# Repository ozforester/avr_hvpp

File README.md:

# avr_hvpp

Simple hvpp programmer on atmega8 and 1602A lcd with twi extention<br>

Kicad schematics and pcb's are placed in hardware folder.
Sure you can even plug mega328 into master socket and<br>
write your code in arduino ide and modify pcb for another package.<br>
Kicad is the most useful tool to change things you like<br>

I'm thinking about coding main menu in C and others: <br>
lcd, twi, adc and hvpp libraries in assembly.<br>
Pure C version I coded was compiled to 8k (w/o a few bytes)<br>
Assembly version is changing now. If you need test one working<br>
You can find a hex file named chiphealer.hex on hardware folder.<br>
Some more errors has to be fixed and I may commit its gas version too<br>

All work except kicad were processed on orange pc.<br>
It's very hard to edit pcb and schematics on orange<br>
(opengl works and 3d model turns but don't do that,<br>
really, beleve me)

And more. I'm learning now. Doing a lot of compromised<br>
steps in programming. These are like a practical answers<br>
to some questions and thus not perfect<br>

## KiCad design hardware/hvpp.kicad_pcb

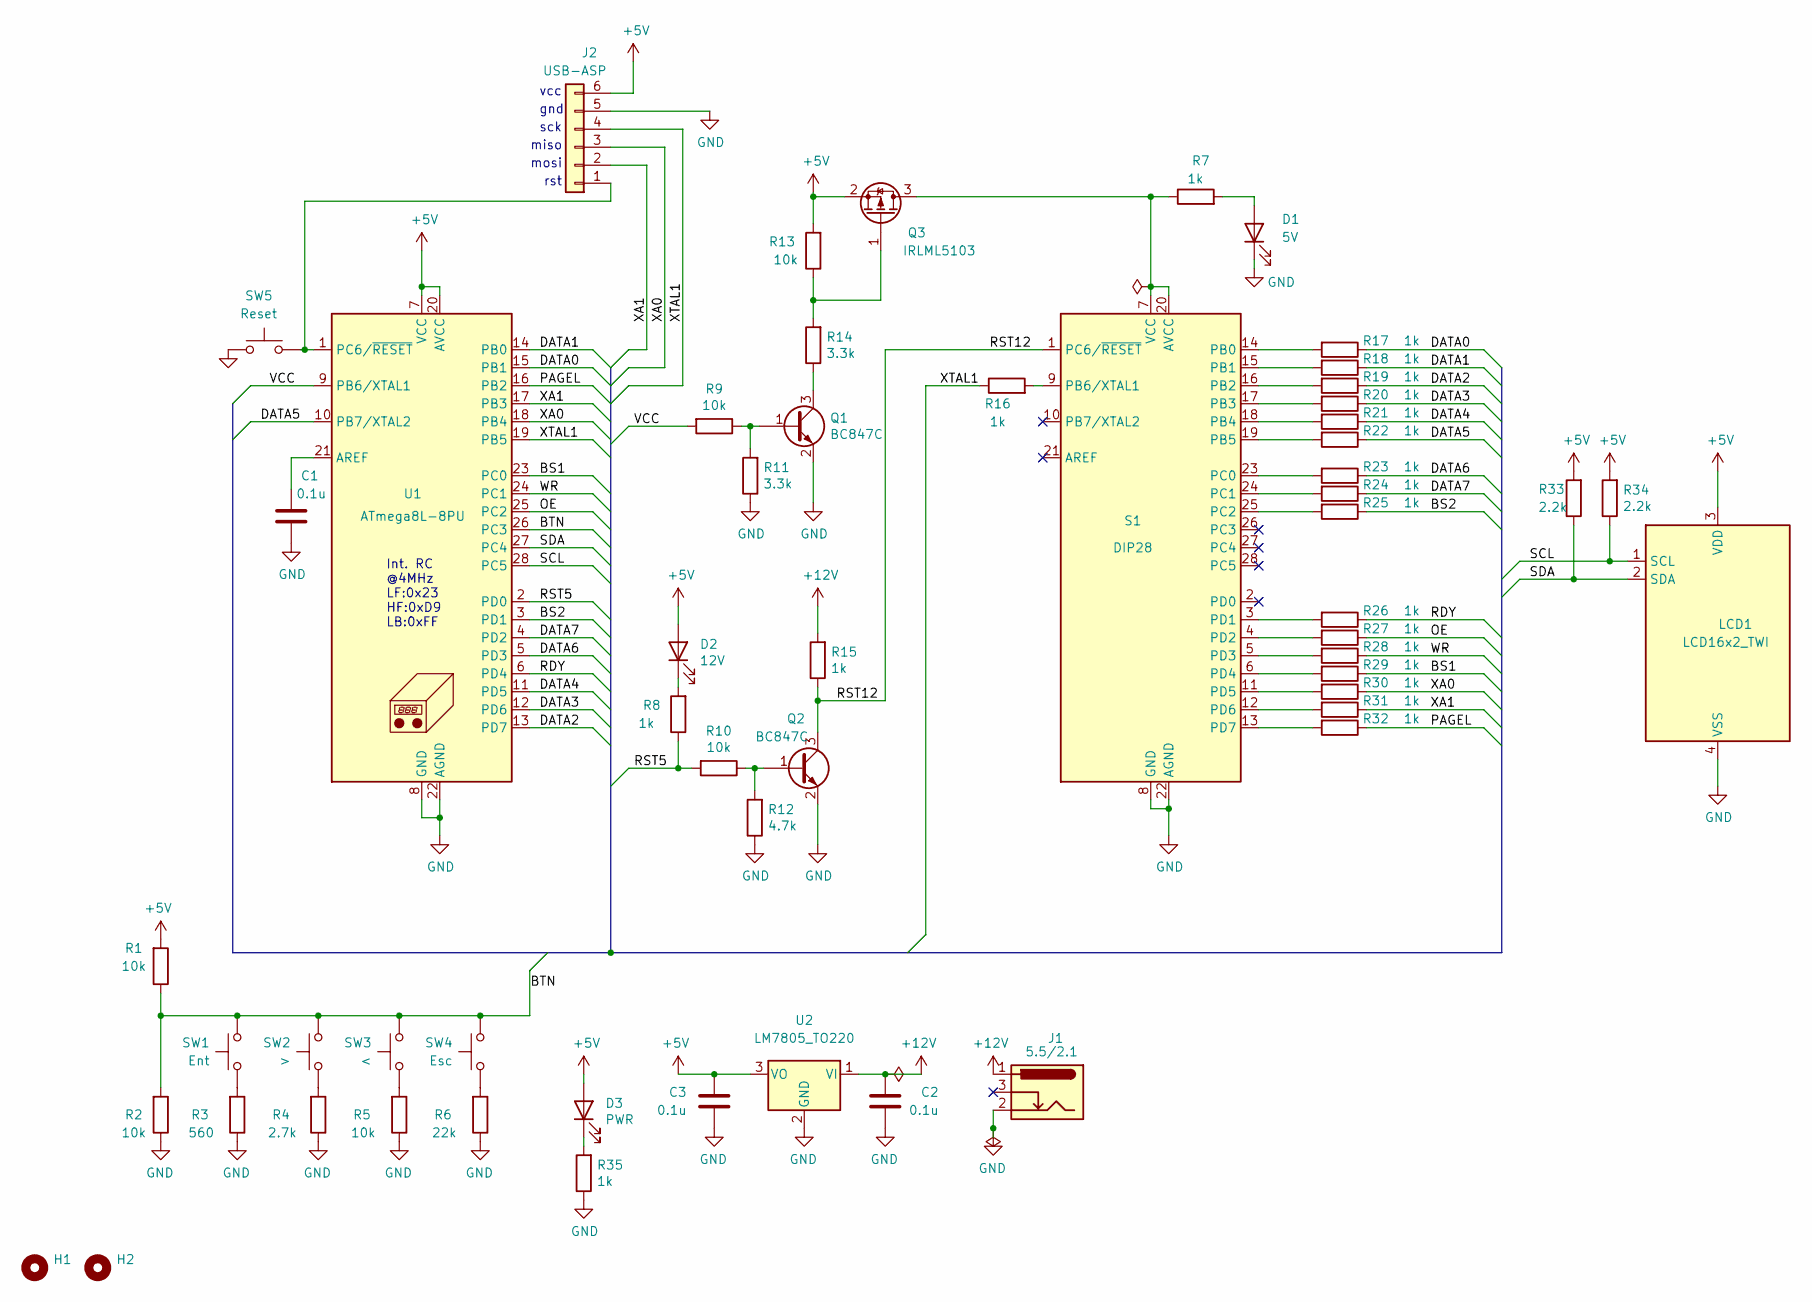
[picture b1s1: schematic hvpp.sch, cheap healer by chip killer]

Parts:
C1, C2, C3: 0.1u; C_0805_2012Metric_Pad1.15x1.40mm_HandSolder
D1: 5V; R_0805_2012Metric_Pad1.15x1.40mm_HandSolder
D2: 12V; R_0805_2012Metric_Pad1.15x1.40mm_HandSolder
D3: PWR; R_0805_2012Metric_Pad1.15x1.40mm_HandSolder
H1, H2: MountingHole; MountingHole_2.2mm_M2_DIN965_Pad
J1: 5.5/2.1; barreljack
J2: USB-ASP; PinHeader_1x06_P2.54mm_Vertical
LCD1: LCD16x2_TWI; 1602A
N1: Housing; DIP-28_W7.62mm
Q1, Q2: BC847C; SOT-23
Q3: IRLML5103; SOT-23
R1, R2, R5, R9, R10, R13: 10k; R_0805_2012Metric_Pad1.15x1.40mm_HandSolder
R3: 560; R_0805_2012Metric_Pad1.15x1.40mm_HandSolder
R4: 2.7k; R_0805_2012Metric_Pad1.15x1.40mm_HandSolder
R6: 22k; R_0805_2012Metric_Pad1.15x1.40mm_HandSolder
R7, R8, R16, R17, R18, R19, R20, R21, R22, R23, R24, R25, R26, R27, R28, R29, R30, R31, R32, R35: 1k; R_0805_2012Metric_Pad1.15x1.40mm_HandSolder
R11, R14: 3.3k; R_0805_2012Metric_Pad1.15x1.40mm_HandSolder
R12: 4.7k; R_0805_2012Metric_Pad1.15x1.40mm_HandSolder
R15: 1k; R_Axial_DIN0207_L6.3mm_D2.5mm_P7.62mm_Horizontal
R33, R34: 2.2k; R_0805_2012Metric_Pad1.15x1.40mm_HandSolder
S1: DIP28; DIP-28_W7.62mm_Socket
SW1: Ent; SW_PUSH_6mm_H5mm
SW2: >; SW_PUSH_6mm_H5mm
SW3: <; SW_PUSH_6mm_H5mm
SW4: Esc; SW_PUSH_6mm_H5mm
SW5: Reset; SW_PUSH_6mm_H5mm
U1: ATmega8L-8PU; DIP-28_W7.62mm_Socket
U2: LM7805_TO220; TO-220-3_Vertical

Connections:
+5V: C3.1, D2.2 (A), D3.2 (A), J2.6, LCD1.3 (VDD), Q3.2 (S), R1.2, R13.2, R33.2, R34.2, U1.7 (VCC), U1.20 (AVCC), U2.3 (VO)
+12V: C2.1, J1.1, R15.2, U2.1 (VI)
/BS1: R29.1, U1.23 (PC0)
/BS2: R25.1, U1.3 (PD1)
/BTN: R1.1, R2.2, SW1.1, SW2.1, SW3.1, SW4.1, U1.26 (PC3)
/DATA0: R17.1, U1.15 (PB1)
/DATA1: R18.1, U1.14 (PB0)
/DATA2: R19.1, U1.13 (PD7)
/DATA3: R20.1, U1.12 (PD6)
/DATA4: R21.1, U1.11 (PD5)
/DATA5: R22.1, U1.10 (PB7/XTAL2)
/DATA6: R23.1, U1.5 (PD3)
/DATA7: R24.1, U1.4 (PD2)
/OE: R27.1, U1.25 (PC2)
/PAGEL: R32.1, U1.16 (PB2)
/RDY: R26.1, U1.6 (PD4)
/RST5: R8.1, R10.2, U1.2 (PD0)
/RST12: Q2.3 (C), R15.1, S1.1 (PC6/~RESET)
/SCL: LCD1.1 (SCL), R34.1, U1.28 (PC5)
/SDA: LCD1.2 (SDA), R33.1, U1.27 (PC4)
/VCC: R9.2, U1.9 (PB6/XTAL1)
/WR: R28.1, U1.24 (PC1)
/XA0: J2.3, R30.1, U1.18 (PB4)
/XA1: J2.2, R31.1, U1.17 (PB3)
/XTAL1: J2.4, R16.1, U1.19 (PB5)
GND: C1.2, C2.2, C3.2, D1.1 (K), J1.2, J2.5, LCD1.4 (VSS), Q1.2 (E), Q2.2 (E), R2.1, R3.1, R4.1, R5.1, R6.1, R11.1, R12.1, R35.1, S1.8 (GND), S1.22 (AGND), SW5.2, U1.8 (GND), U1.22 (AGND), U2.2 (GND)
unnamed: C1.1, U1.21 (AREF)
unnamed: D1.2 (A), R7.2
unnamed: D2.1 (K), R8.2
unnamed: D3.1 (K), R35.2
unnamed: J2.1, SW5.1, U1.1 (PC6/~RESET)
unnamed: Q1.1 (B), R9.1, R11.2
unnamed: Q1.3 (C), R14.1
unnamed: Q2.1 (B), R10.1, R12.2
unnamed: Q3.1 (G), R13.1, R14.2
unnamed: Q3.3 (D), R7.1, S1.7 (VCC), S1.20 (AVCC)
unnamed: R3.2, SW1.2
unnamed: R4.2, SW2.2
unnamed: R5.2, SW3.2
unnamed: R6.2, SW4.2
unnamed: R16.2, S1.9 (PB6/XTAL1)
unnamed: R17.2, S1.14 (PB0)
unnamed: R18.2, S1.15 (PB1)
unnamed: R19.2, S1.16 (PB2)
unnamed: R20.2, S1.17 (PB3)
unnamed: R21.2, S1.18 (PB4)
unnamed: R22.2, S1.19 (PB5)
unnamed: R23.2, S1.23 (PC0)
unnamed: R24.2, S1.24 (PC1)
unnamed: R25.2, S1.25 (PC2)
unnamed: R26.2, S1.3 (PD1)
unnamed: R27.2, S1.4 (PD2)
unnamed: R28.2, S1.5 (PD3)
unnamed: R29.2, S1.6 (PD4)
unnamed: R30.2, S1.11 (PD5)
unnamed: R31.2, S1.12 (PD6)
unnamed: R32.2, S1.13 (PD7)

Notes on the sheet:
mosi
miso
sck
gnd
vcc
rst
Int. RC @4MHz LF:0x23 HF:0xD9 LB:0xFF

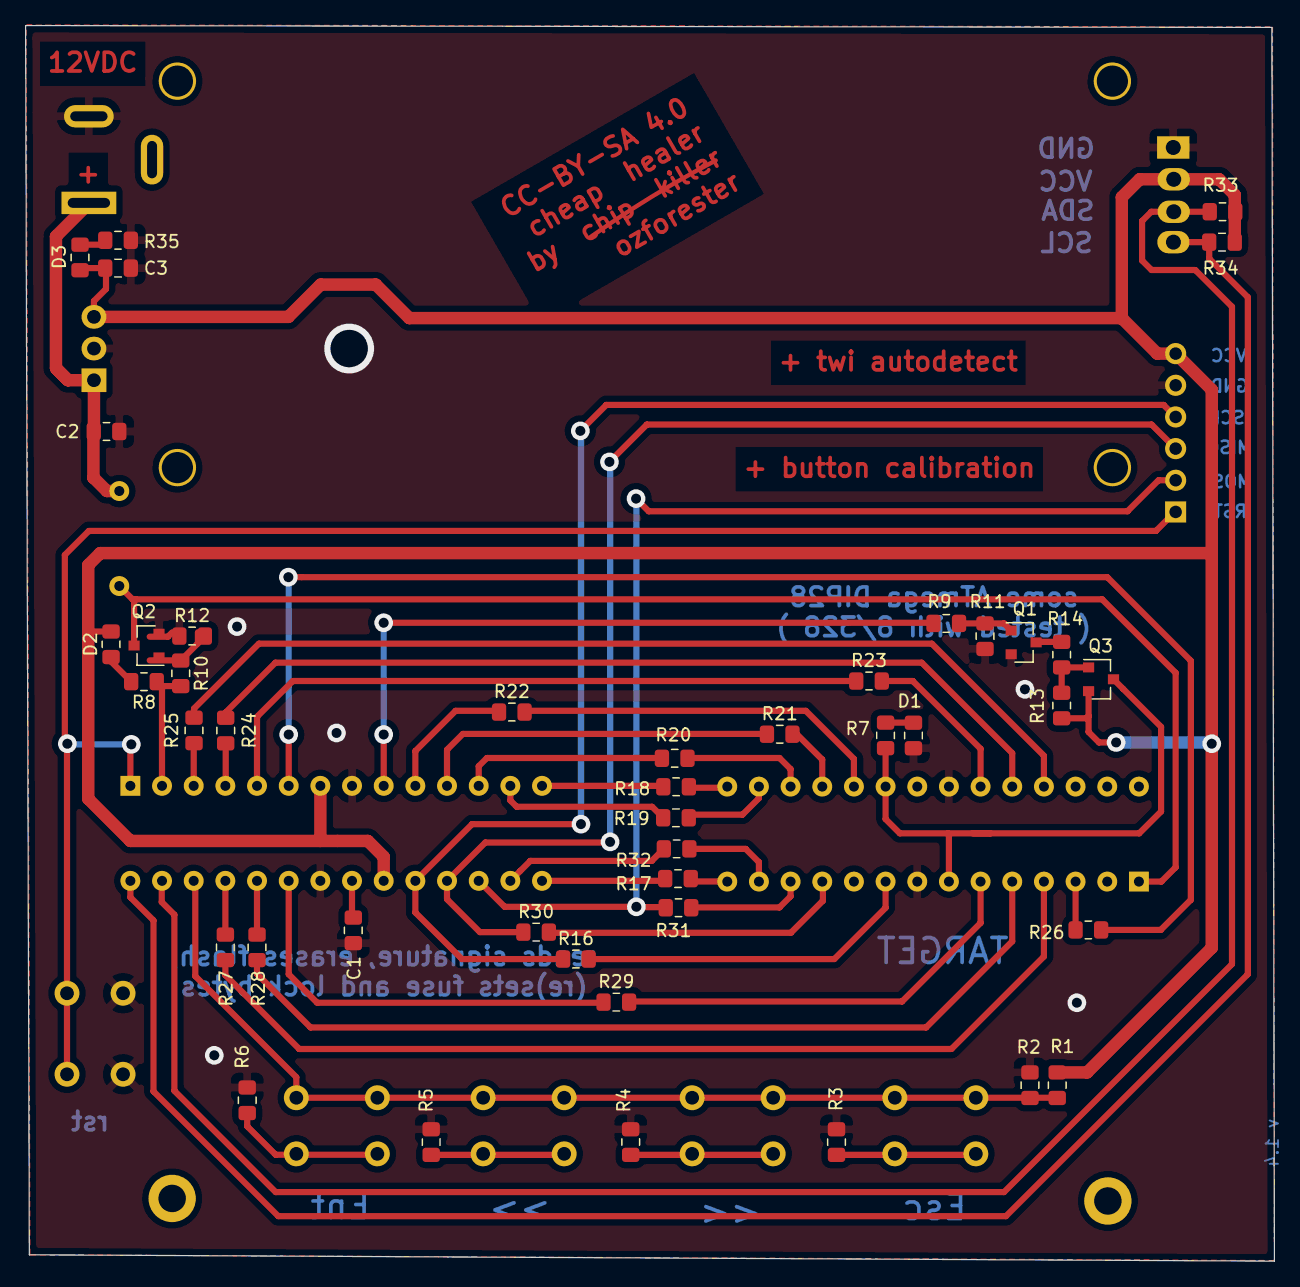
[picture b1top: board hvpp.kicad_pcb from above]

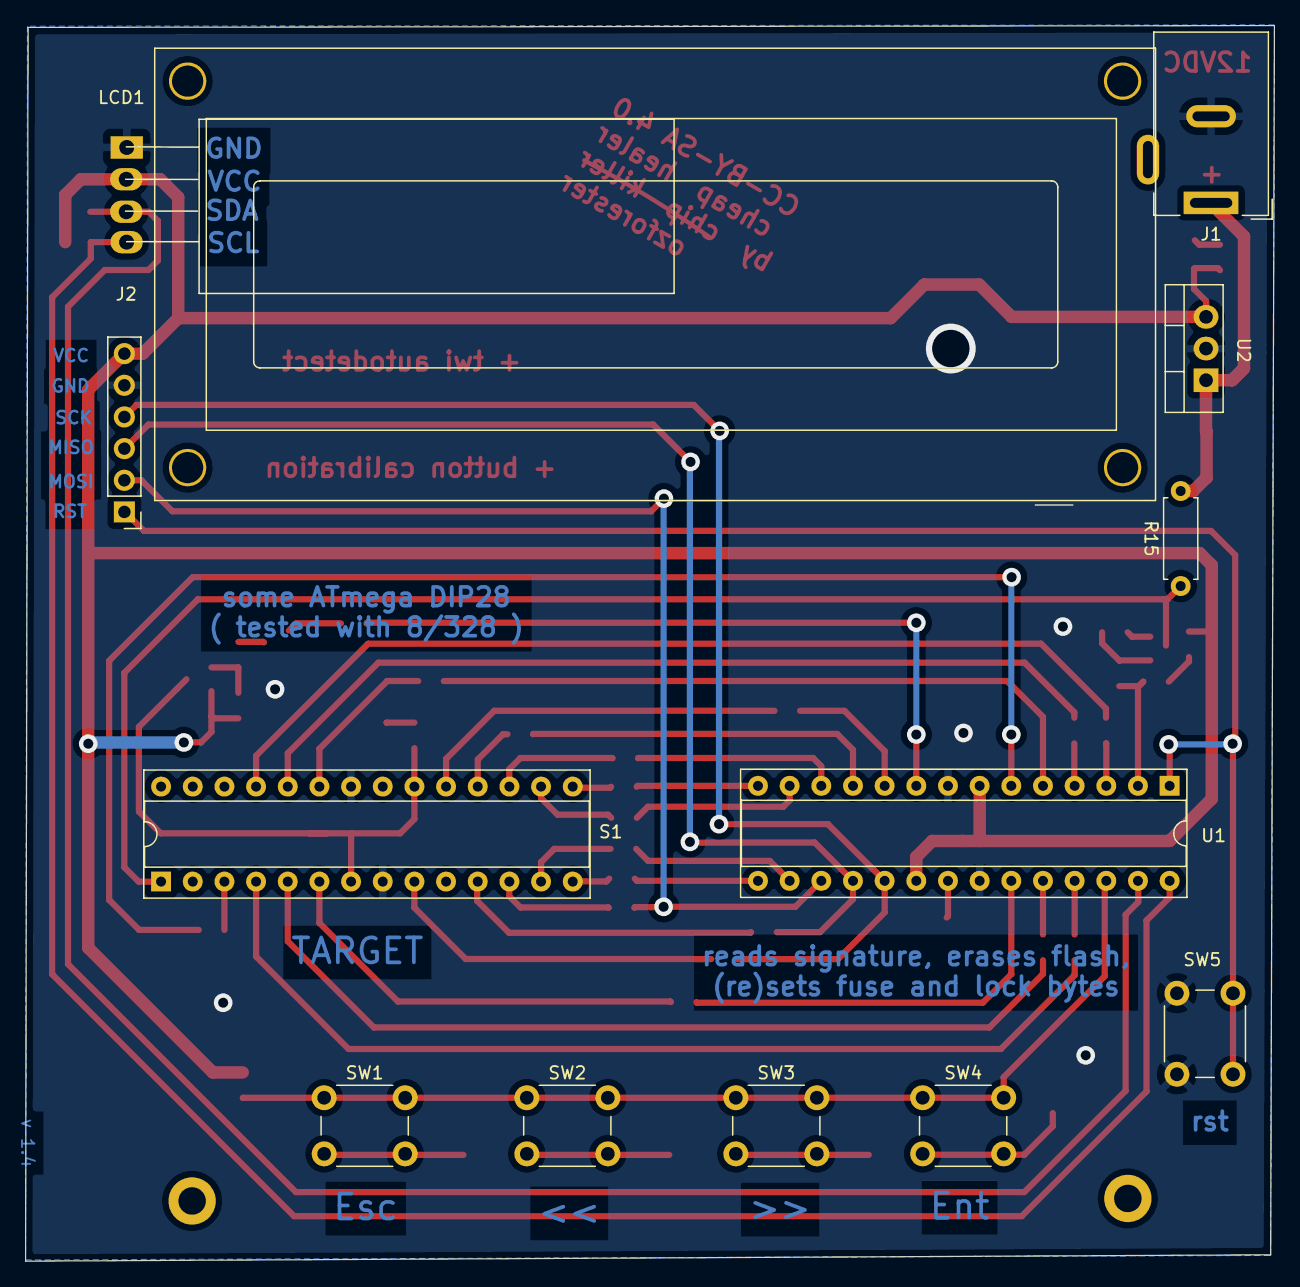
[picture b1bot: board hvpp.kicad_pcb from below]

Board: 2 copper layers, 100.2 x 99.1 mm, 57 parts (12 on the bottom side), 57 nets.

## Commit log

2021-05-20 test
2021-05-20 just more chars on it
2021-05-20 initial
2021-05-22 minor correction
2021-05-22 deleted
2021-06-05 misspelling
2021-06-05 debugging
2021-06-05 spelling
2021-06-06 pure assembly version
2021-06-06 minor change
2021-06-06 nothing special
2021-06-06 nothig special
2021-06-12 a little time to work
2021-06-13 kkjkj
2021-06-13 worktime
2021-06-14 work time
2021-07-03 a few time to continue
2021-09-04 lost carry bit in ascii conversion
2021-09-04 carry bit fixed in ascii

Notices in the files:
hardware/hvpp.kicad_pcb:
CC-BY-SA 4.0
hardware/hvpp.sch:
CC-BY-SA 4.0 license
